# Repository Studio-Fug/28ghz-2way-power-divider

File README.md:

# 28 GHz two-way power divider / combiner

Experimental YAPNR inverse-designed microstrip Wilkinson coupon targeting the Knowles PDW07630's 24–32 GHz small-signal performance. **Revision A fails the return-loss and loss requirements in exported-footprint simulation. It is not a validated replacement for PDW07630.**

The 40 × 36 mm board uses a 0.51 mm RO4350B core, three Southwest Microwave 1092-03A-6 2.92 mm edge launches, equal-length output feeds and a 100 ohm Vishay CH02016 resistor. J1 is SUM, J2/J3 are the two inputs/outputs. The board shot is a KiCad render of the actual copper and mechanical lands; connectors and resistor are not installed in the render.

- [Requirements model](requirements/model.yaml): 3 user needs, 15 requirements and 6 verification methods.
- [Validation report](reports/validation.md): acceptance criteria, grid comparison and links to simulation results.
- [rules_requirements traceability](reports/traceability.md), [HTML](reports/traceability.html), [JSON](reports/traceability.json), [gap queue](reports/gaps.json).
- [KiCad PCB](output/test-board/rf-combiner-test.kicad_pcb), [project](output/test-board/rf-combiner-test.kicad_pro), [BOM](output/test-board/BOM.csv).
- [Fabrication ZIP](output/test-board/rf-combiner-revA-fabrication.zip), [fabrication/assembly notes](FABRICATION.md). Layout DRC passes; RF acceptance does not.
- [Exported RF footprint](runs/jlc20mil/footprint.kicad_mod), [simulation metrics](runs/jlc20mil/comparison.json), [artifact hashes](reports/artifact-manifest.json).

## Requirements and sources

The baseline is the [Knowles datasheet](https://www.knowlescapacitors.com/getattachment/Products/Microwave-Products/Power-Dividers/PDW07630_DATASHEET.pdf?lang=en-US), preserved as [reference PDF](reference/PDW07630_DATASHEET.pdf): 24–32 GHz, return loss ≥15 dB, isolation ≥14 dB, excess insertion loss ≤0.7 dB, amplitude balance ±0.5 dB, phase balance ±5°. The combiner is specified for equal-amplitude, equal-phase inputs. Its 5 W combining rating is not qualified for this coupon.

The workflow follows [YAPNR RF inverse design](https://studio-fug.github.io/yapnr/docs/rf-inverse-design.html). The user's final stackup selection superseded the earlier 10 mil option: **0.51 mm core and 2.92 mm launches**. A larger board footprint was accepted. [DUT optimization spec](specs/dut-optimization.json) holds stricter optimization goals (20 dB return loss, 17 dB isolation, 0.5 dB excess loss); [requirements/model.yaml](requirements/model.yaml) retains the datasheet minimum acceptance thresholds.

## Whole-assembly validation gate

[spec.json](spec.json) is the authoritative project specification. It requires simulation of the complete populated assembly at the three 2.92 mm coaxial mating planes, including the actual feed bends, launch transitions, connectors, ground/vias, finite board, material losses and resistor package. All assembly RF limits include fixture losses. DUT-only simulation and DRC cannot satisfy this gate. One YAPNR-owned assembly SSoT must drive all backend adapters, with common geometry, materials, component mappings and reference planes; client projects supply declarative design/requirements data and must not write custom solver-model or mesh code.

**Assembly simulation is BLOCKED, not completed.** [Readiness report](reports/assembly-validation.json) records missing qualified connector/material models, resistor reference-plane qualification and a supported full-assembly SSoT/adapter workflow. YAPNR does provide suitable openEMS/PALACE engines and partial KiCad/mesh/config integration; the gap is the end-to-end minimal-code assembly path ([issue #97](https://github.com/Studio-Fug/yapnr/issues/97)). The [importer audit](reports/backend-capability-audit.json) also found omitted floating copper and NPTH geometry errors. A [Vishay 100 ohm candidate model](models/resistor/CH02016F_P_100R.s2p) is included, with [provenance](models/resistor/provenance.json); it has 100 ohm normalization and must be qualified before co-simulation.

Run `python3 scripts/check_assembly_readiness.py` to regenerate the readiness report. It intentionally returns a nonzero exit status until assembly simulation is possible, and never grants validation from readiness alone. REQ-13 through REQ-15 track complete-assembly RF acceptance, model coverage and numerical/tolerance evidence. REQ-11 remains the separate measured bench acceptance requirement.

## Reproduction

Docker is required for RF simulation. YAPNR is an external dependency, pinned by [upstream image digest, Git revision and archive checksum](dependencies/yapnr.json). The run scripts build a cached runtime image from [Dockerfile](Dockerfile), fetching upstream source during the build; no YAPNR source is vendored in this repository. The upstream image includes Torch 2.3.1 and the native FDTD backend, but its wheel omits `yapnr.rf.export` ([upstream issue #96](https://github.com/Studio-Fug/yapnr/issues/96)). Until that packaging defect is fixed, the derived image loads the complete pinned upstream Python package from `/opt/yapnr-dependency`, retaining the base image's matching native solver. This is a temporary source-dependency workaround, not a `pip install git+...` installation. Build-time imports and native-source checks fail if the dependency is incomplete or mismatched. Containers are bounded to two CPU cores and 6 GB RAM. The first build needs network access; later builds reuse Docker layers.

```sh
./run-container.sh > optimization.log 2>&1
./run-validation.sh > validation.log 2>&1
```

The committed run contains the checkpoint, optimization history, exported footprint, full complex S-parameter sweeps and mesh masks. Rerunning optimization resumes the checkpoint; move `runs/jlc20mil` aside first for a fresh run. Validation simulates the exported polygons on 0.15, 0.075 and 0.05 mm lateral grids with 4, 6 and 8 substrate cells. Each validation sweep has 81 frequencies from 24 to 32 GHz and 50 ohm reference impedance at the DUT boundary planes. The complete fixture is not included in that simulation.

To regenerate the requirements report with Python 3.9+:

```sh
python3 -m venv .venv
. .venv/bin/activate
pip install -r requirements/requirements.txt
./scripts/report.sh
```

`--fail-on none` permits report generation with known design failures; it does not change their verdicts. Each evidence case owns exactly one requirement. The verification lock pins the expected case sets; the evidence records simulation file paths and SHA-256 hashes.

Build the PCB using KiCad 10's `pcbnew` Python bindings, then run native DRC:

```sh
python3 build_board.py runs/jlc20mil/footprint.kicad_mod
kicad-cli pcb drc --exit-code-violations --format json \
  --output output/test-board/drc.json output/test-board/rf-combiner-test.kicad_pcb
```

The build converts the continuous multi-terminal footprint graphic to a custom-pad primitive without changing its polygon coordinates, enabling KiCad's connectivity checks. The three microwave port numbers share a DC net, as expected for a Wilkinson copper island.

## Timing

[timing.json](output/timing.json) records the available first-prompt timestamp, optimizer duration, completion of validation, and repository delivery. The first-prompt timestamp may have been replayed on restart; any earlier unrecorded interval is excluded. Completing a validation procedure does not mean the design passed validation.

## Third-party material

YAPNR is an external AGPL-3.0 dependency; its source and license are available in the [upstream repository](https://github.com/Studio-Fug/yapnr). Manufacturer documents retain their respective copyrights. Tool revisions and image digest are recorded in [dependencies/yapnr.json](dependencies/yapnr.json) and [result.json](runs/jlc20mil/result.json). The initial simulations used a local snapshot of the same revision. Every Python module was byte-compared with the fetched upstream source and matched, and the native source hash also matches; historical simulation artifacts are unchanged.

A plot of the recorded validation sweeps is in [simulation-comparison.png](reports/simulation-comparison.png); regenerate it with `python3 scripts/plot_results.py` after installing NumPy and Matplotlib.

To verify that the external dependency reproduces the original simulation, run:

```sh
./scripts/build-runtime.sh
docker run --rm --cpus 2 --memory 6g -v "$PWD:/project" -w /tmp \
  -e OPENBLAS_NUM_THREADS=1 -e OMP_NUM_THREADS=2 -e YAPNR_RF_THREADS=2 \
  -e YAPNR_RF_REQUIRE_NATIVE=1 --entrypoint python3 \
  28ghz-divider-rf:57df5897-1 -u /project/scripts/check_dependency.py
```

[Recorded dependency check](reports/dependency-smoke.json) compares the full complex coarse-grid S matrix, with exact equality required.

The [public Knowledge PoC](knowledge/README.md) packages requirements, simulation evidence and commit-pinned board artifacts into a signed object, preserving failed and missing validation.

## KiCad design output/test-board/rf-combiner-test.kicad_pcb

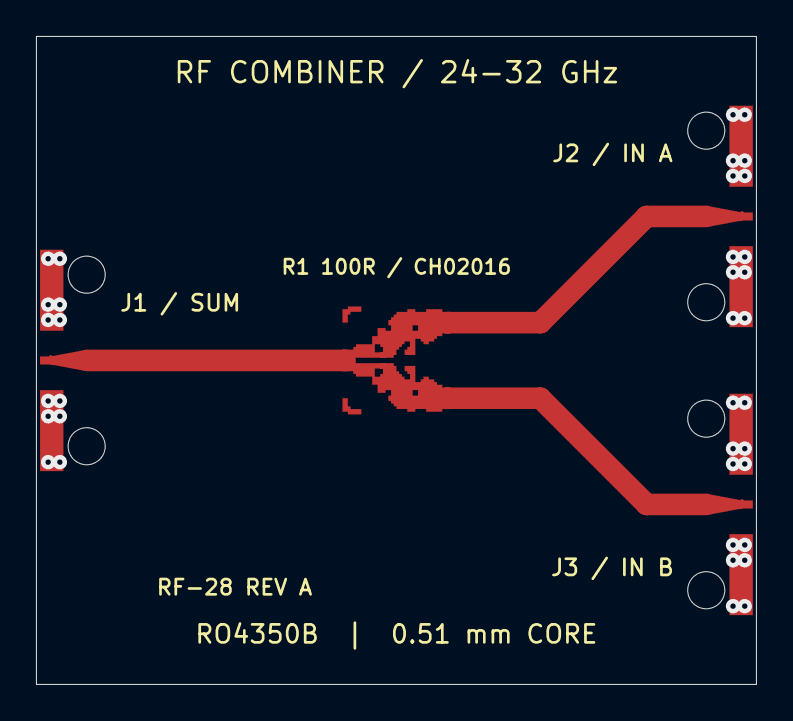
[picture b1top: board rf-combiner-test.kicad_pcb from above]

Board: 2 copper layers, 40.0 x 36.0 mm, 7 parts (0 on the bottom side), 2 nets.

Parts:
J1: 1092-03A-6; SWM_1092-03A-6_Left
J2, J3: 1092-03A-6; SWM_1092-03A-6_Right
RF1: RF_pdw07630-comparable-jlc-ro4350b-20mil; footprint
TP1, TP2, TP3: (no value)

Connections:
GND: J1.2, J1.3, J2.2, J2.3, J3.2, J3.3
RF: J1.1, J2.1, J3.1, RF1.1, RF1.2, RF1.3, RF1.4, RF1.5, TP1.1, TP2.1, TP3.1
